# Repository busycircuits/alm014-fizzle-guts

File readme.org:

* ALM014 FIZZLE GUTS

[[alm014.png]]

** Introduction

The ALM Busy Circuits 'Fizzle guts' is a Eurorack dual low pass filter
and VCA that uses a 'donor' filter MB87186 chip from a Casio FZ1
sampler. It was originally designed in 2014 as a fun side project and
only approx 30 of the original units were made. With no plans to make
any more, we have open sourced the pcb design files (eagle), avr
microcontroller code and a basic panel design so others can make there
own and add customisations and/or improvements.

A built module features two filter cores A & B with voltage and direct
controlled resonance and cut off as well as a 'DCA' (a digital
controlled vca). There is also a mix output. Expect a weird murky
sounding filter which can squeek and blip when modulated but can
really squelch up nice.

You will need a donor 'MB87186' IC desolded from a real FZ1 or FZ1M
synth. They each contain 4 and the IC is usually marked 'FM1' with a
date code below. The IC then connects to the DIL socket on the rear of
the module.

For more information on the MB87186 (and from what much of the code
was based on) see http://www.buchty.net/casio/dcf.html

*PLEASE NOTE EVERYTHING IS PROVIDED AS IS. WE ARE UNABLE PROVIDE ANY SUPPORT TO ANYONE ATTEMPTING TO USE THESE FILES*

** Building and flashing the firmware

You'll need a basic 'usbtiny' AVR programmer.

You'll need to install avr-gcc and avrdude.

/(On mac using brew..)/
#+BEGIN_SRC
brew tap osx-cross/avr
brew install avr-gcc
brew install avrdude
#+END_SRC

Type 'make' in the firmare/ directory to compile the source code and
then run './flash.sh' (with your programmer connected) to program the
Fizzle.

** License

Code: MIT license.

Hardware: cc-by-sa-3.0

** Guidelines for derivative works

*ALM is a registered trademark.*

The name "ALM" should not be used on any of the derivative works you create from these files.

We kindly ask to do not name any derivatives 'FIZZLE GUTS' but give it a new name.

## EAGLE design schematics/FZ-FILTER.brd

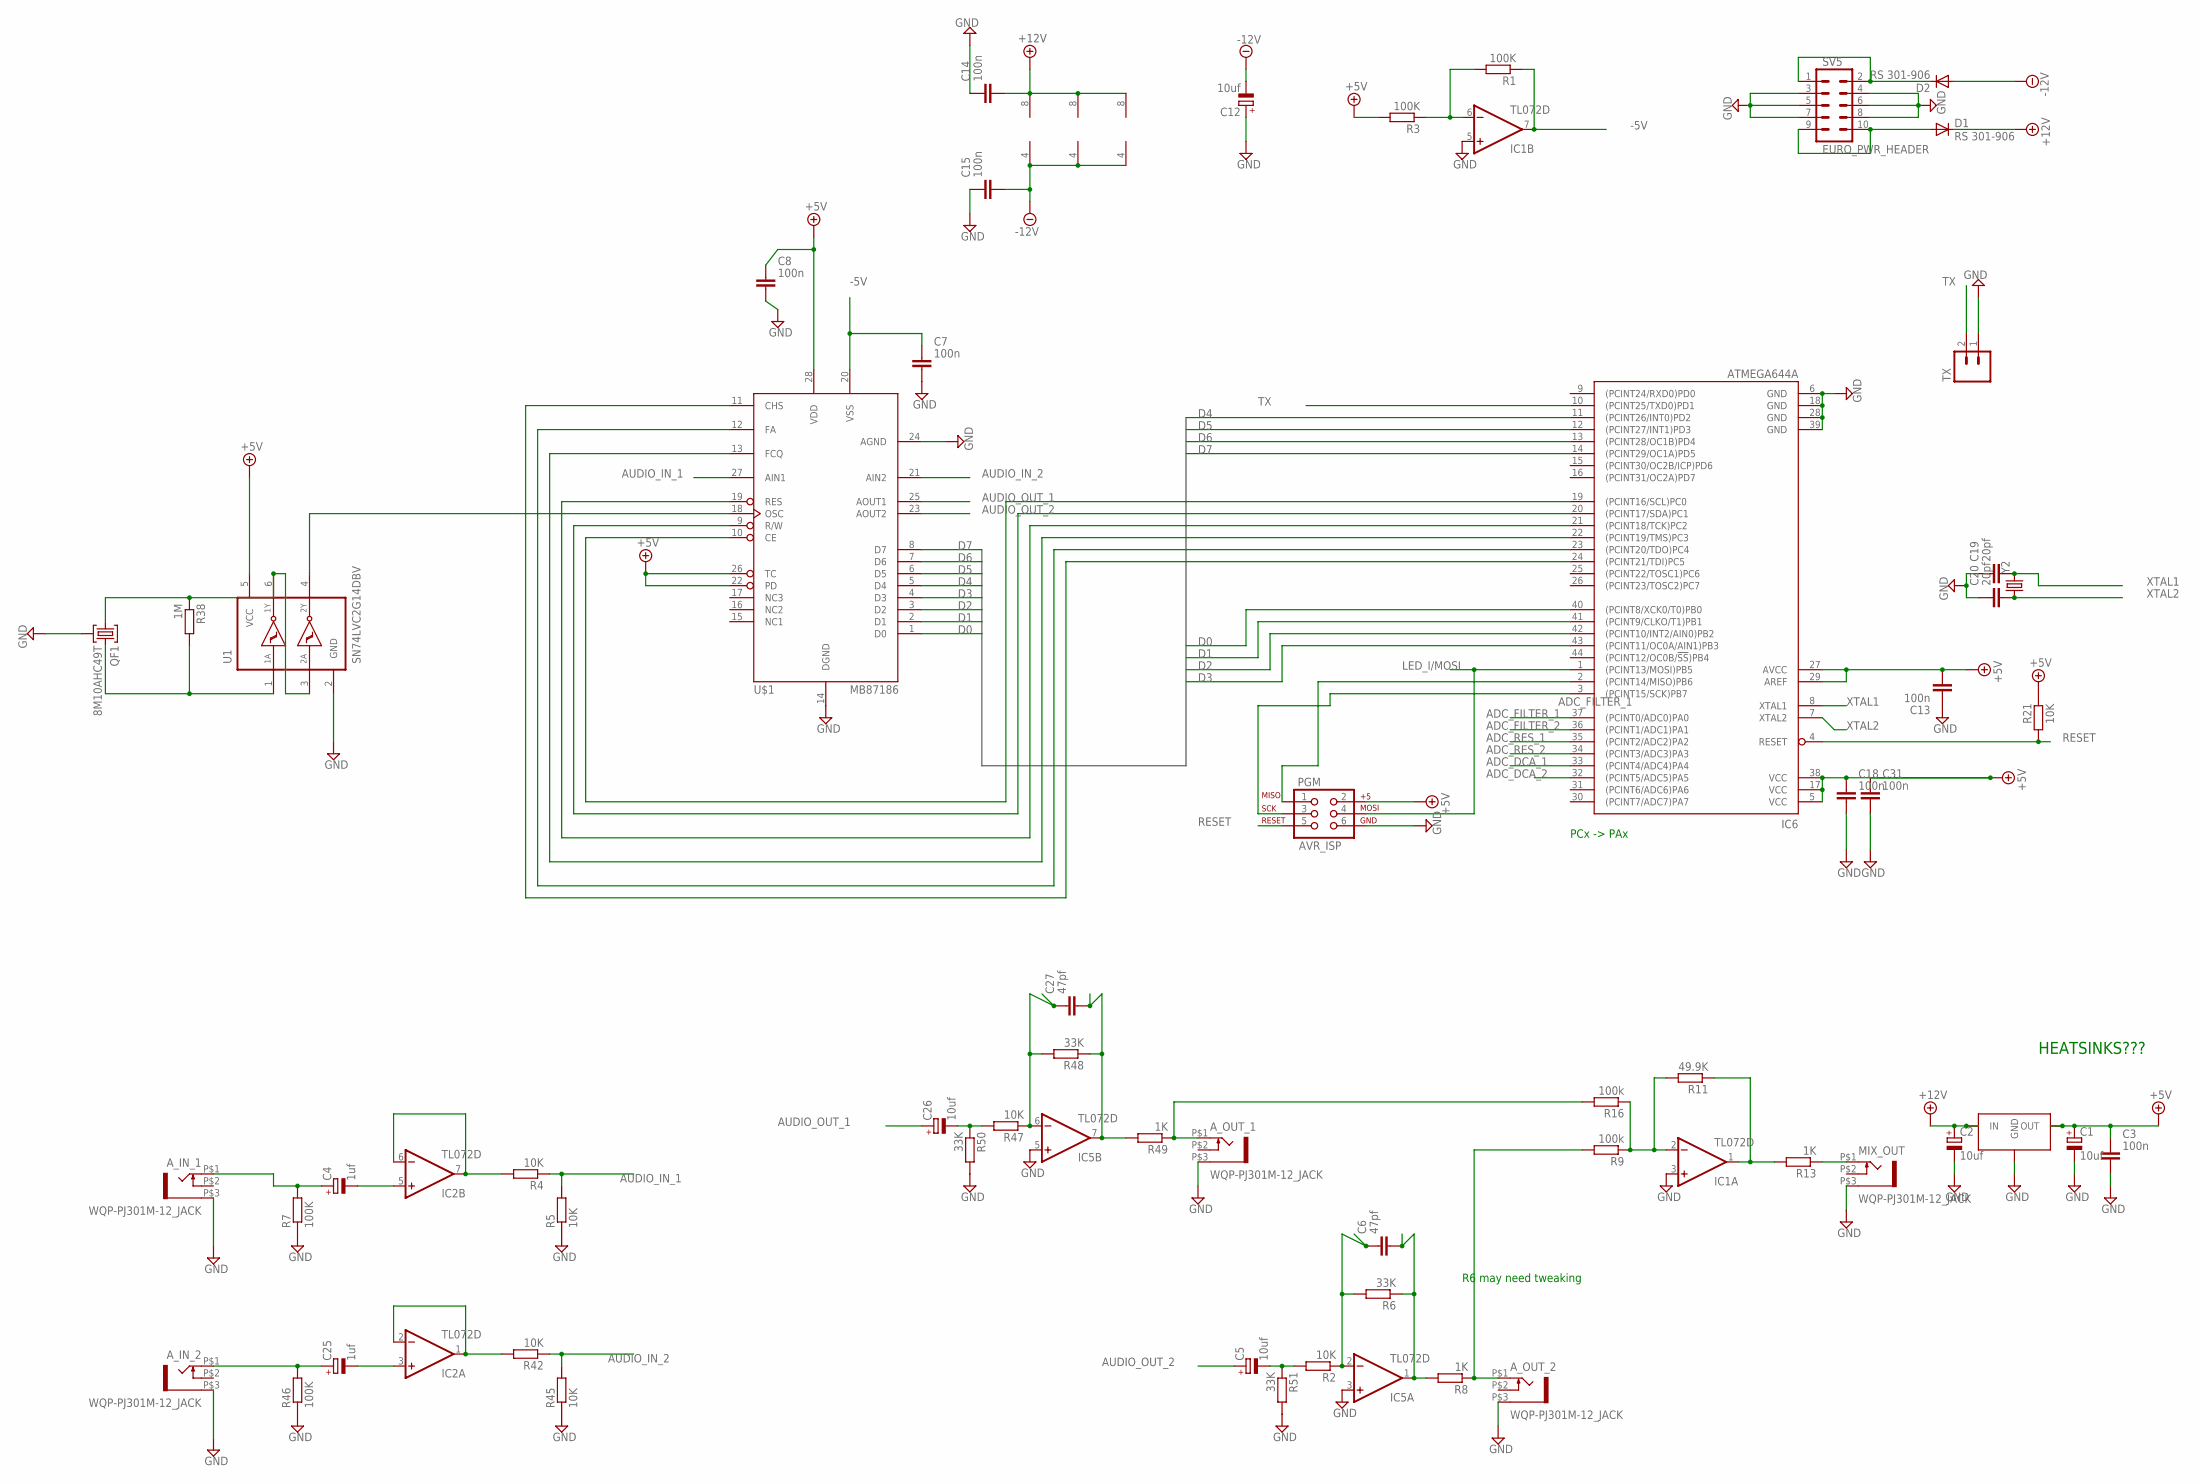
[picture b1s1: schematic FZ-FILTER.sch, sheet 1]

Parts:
A_IN_1, A_IN_2: WQP-PJ301M-12_JACK
A_OUT_1, A_OUT_2: WQP-PJ301M-12_JACK
C1, C2, C5, C12, C26: 10uf; PANASONIC_B
C3, C7, C8, C13, C14, C15, C18, C31: 100n; C0603
C4, C25: 1uf; PANASONIC_B
C6, C27: 47pf; C0603
C19, C20: 20pf; C0603
D1, D2: RS 301-906; SMB-DIODE
IC1, IC2, IC5: TL072D; SO08
IC6: ATMEGA644A; TQFP44
MIX_OUT: WQP-PJ301M-12_JACK
PGM: AVR_ISP; 2X3
QF1: 8M10AHC49T; HC49U
R1, R3, R7, R46: 100K; R0603
R2, R4, R5, R21, R42, R45, R47: 10K; R0603
R6, R48, R50, R51: 33K; R0603
R8, R13, R49: 1K; R0603
R9, R16: 100k; R0603
R11: 49.9K; R0603
R38: 1M; R0603
SV5: EURO_PWR_HEADER
TX: M02PTH; 1X02
U1: SN74LVC2G14DBV; SOT23-6
U3: 7805; VREG-7805-DPAK2
U$1: MB87186; DIP28
Y2: CRYSTALSMD; HC49UP

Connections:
+5V: C1.+, C3.1, C8.1, C13.2, C18.1, C31.1, IC6.5 (VCC), IC6.17 (VCC), IC6.27 (AVCC), IC6.29 (AREF), IC6.38 (VCC), PGM.2, R3.2, R21.2, U1.5 (VCC), U3.VOUT (OUT), U$1.22 (PD), U$1.26 (TC), U$1.28 (VDD); also elsewhere on the board
+12V: C2.+, C14.2, D1.C, IC1.8 (V+), IC2.8 (V+), IC5.8 (V+), U3.VIN (IN); also elsewhere on the board
-5V: C7.1, IC1.7 (OUT), R1.1, U$1.20 (VSS); also elsewhere on the board
-12V: C12.-, C15.2, D2.A, IC1.4 (V-), IC2.4 (V-), IC5.4 (V-); also elsewhere on the board
ADC_DCA_1: IC6.33 ((PCINT4/ADC4)PA4); also elsewhere on the board
ADC_DCA_2: IC6.32 ((PCINT5/ADC5)PA5); also elsewhere on the board
ADC_FILTER_1: IC6.37 ((PCINT0/ADC0)PA0); also elsewhere on the board
ADC_FILTER_2: IC6.36 ((PCINT1/ADC1)PA1); also elsewhere on the board
ADC_MISO: IC6.2 ((PCINT14/MISO)PB6), PGM.1
ADC_RES_1: IC6.35 ((PCINT2/ADC2)PA2); also elsewhere on the board
ADC_RES_2: IC6.34 ((PCINT3/ADC3)PA3); also elsewhere on the board
ADC_SCK: IC6.3 ((PCINT15/SCK)PB7), PGM.3
AUDIO_IN_1: R4.1, R5.2, U$1.27 (AIN1)
AUDIO_IN_2: R42.1, R45.2, U$1.21 (AIN2)
AUDIO_OUT_1: C26.+, U$1.25 (AOUT1)
AUDIO_OUT_2: C5.+, U$1.23 (AOUT2)
D0: IC6.40 ((PCINT8/XCK0/T0)PB0), U$1.1 (D0)
D1: IC6.41 ((PCINT9/CLKO/T1)PB1), U$1.2 (D1)
D2: IC6.42 ((PCINT10/INT2/AIN0)PB2), U$1.3 (D2)
D3: IC6.43 ((PCINT11/OC0A/AIN1)PB3), U$1.4 (D3)
D4: IC6.11 ((PCINT26/INT0)PD2), U$1.5 (D4)
D5: IC6.12 ((PCINT27/INT1)PD3), U$1.6 (D5)
D6: IC6.13 ((PCINT28/OC1B)PD4), U$1.7 (D6)
D7: IC6.14 ((PCINT29/OC1A)PD5), U$1.8 (D7)
GND: A_IN_1.P$3 (1), A_IN_2.P$3 (1), A_OUT_1.P$3 (1), A_OUT_2.P$3 (1), C1.-, C2.-, C3.2, C7.2, C8.2, C12.+, C13.1, C14.1, C15.1, C18.2, C19.1, C20.1, C31.2, IC1.3 (+IN), IC1.5 (+IN), IC5.3 (+IN), IC5.5 (+IN), IC6.6 (GND), IC6.18 (GND), IC6.28 (GND), IC6.39 (GND), MIX_OUT.P$3 (1), PGM.6, QF1.2, R5.1, R7.1, R45.1, R46.1, R50.2, R51.2, SV5.3, SV5.4, SV5.5, SV5.6, SV5.7, SV5.8, TX.1, U1.2 (GND), U3.GND, U$1.14 (DGND), U$1.24 (AGND); also elsewhere on the board
LED_I/MOSI: IC6.1 ((PCINT13/MOSI)PB5), PGM.4
unnamed: D2.C, SV5.1, SV5.2
unnamed: IC1.6 (-IN), R1.2, R3.1
unnamed: D1.A, SV5.9, SV5.10
unnamed: IC2.6 (-IN), IC2.7 (OUT), R4.2
unnamed: C6.1, IC5.2 (-IN), R2.1, R6.2
unnamed: C6.2, IC5.1 (OUT), R6.1, R8.2
unnamed: C5.-, R2.2, R51.1
unnamed: A_OUT_1.P$1 (2), R16.2, R49.1
unnamed: IC1.2 (-IN), R9.1, R11.2, R16.1
unnamed: IC1.1 (OUT), R11.1, R13.2
unnamed: A_OUT_2.P$1 (2), R8.1, R9.2
unnamed: C4.-, IC2.5 (+IN)
unnamed: A_IN_1.P$1 (2), C4.+, R7.2
unnamed: C25.-, IC2.3 (+IN)
unnamed: IC2.1 (OUT), IC2.2 (-IN), R42.2
unnamed: A_IN_2.P$1 (2), C25.+, R46.2
unnamed: C27.1, IC5.6 (-IN), R47.1, R48.2
unnamed: C27.2, IC5.7 (OUT), R48.1, R49.2
unnamed: C26.-, R47.2, R50.1
unnamed: MIX_OUT.P$1 (2), R13.1
unnamed: IC6.19 ((PCINT16/SCL)PC0), U$1.10 (CE)
unnamed: IC6.20 ((PCINT17/SDA)PC1), U$1.9 (R/W)
unnamed: IC6.21 ((PCINT18/TCK)PC2), U$1.19 (RES)
unnamed: IC6.22 ((PCINT19/TMS)PC3), U$1.13 (FCQ)
unnamed: IC6.23 ((PCINT20/TDO)PC4), U$1.12 (FA)
unnamed: IC6.24 ((PCINT21/TDI)PC5), U$1.11 (CHS)
unnamed: U1.4 (2Y), U$1.18 (OSC)
unnamed: QF1.1, R38.1, U1.3 (2A), U1.6 (1Y)
unnamed: QF1.3, R38.2, U1.1 (1A)
RESET: IC6.4 (RESET), PGM.5, R21.1
TX: IC6.10 ((PCINT25/TXD0)PD1), TX.2
XTAL1: C19.2, IC6.8 (XTAL1), Y2.2
XTAL2: C20.2, IC6.7 (XTAL2), Y2.1

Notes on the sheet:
PCx -> PAx
HEATSINKS???
R6 may need tweaking

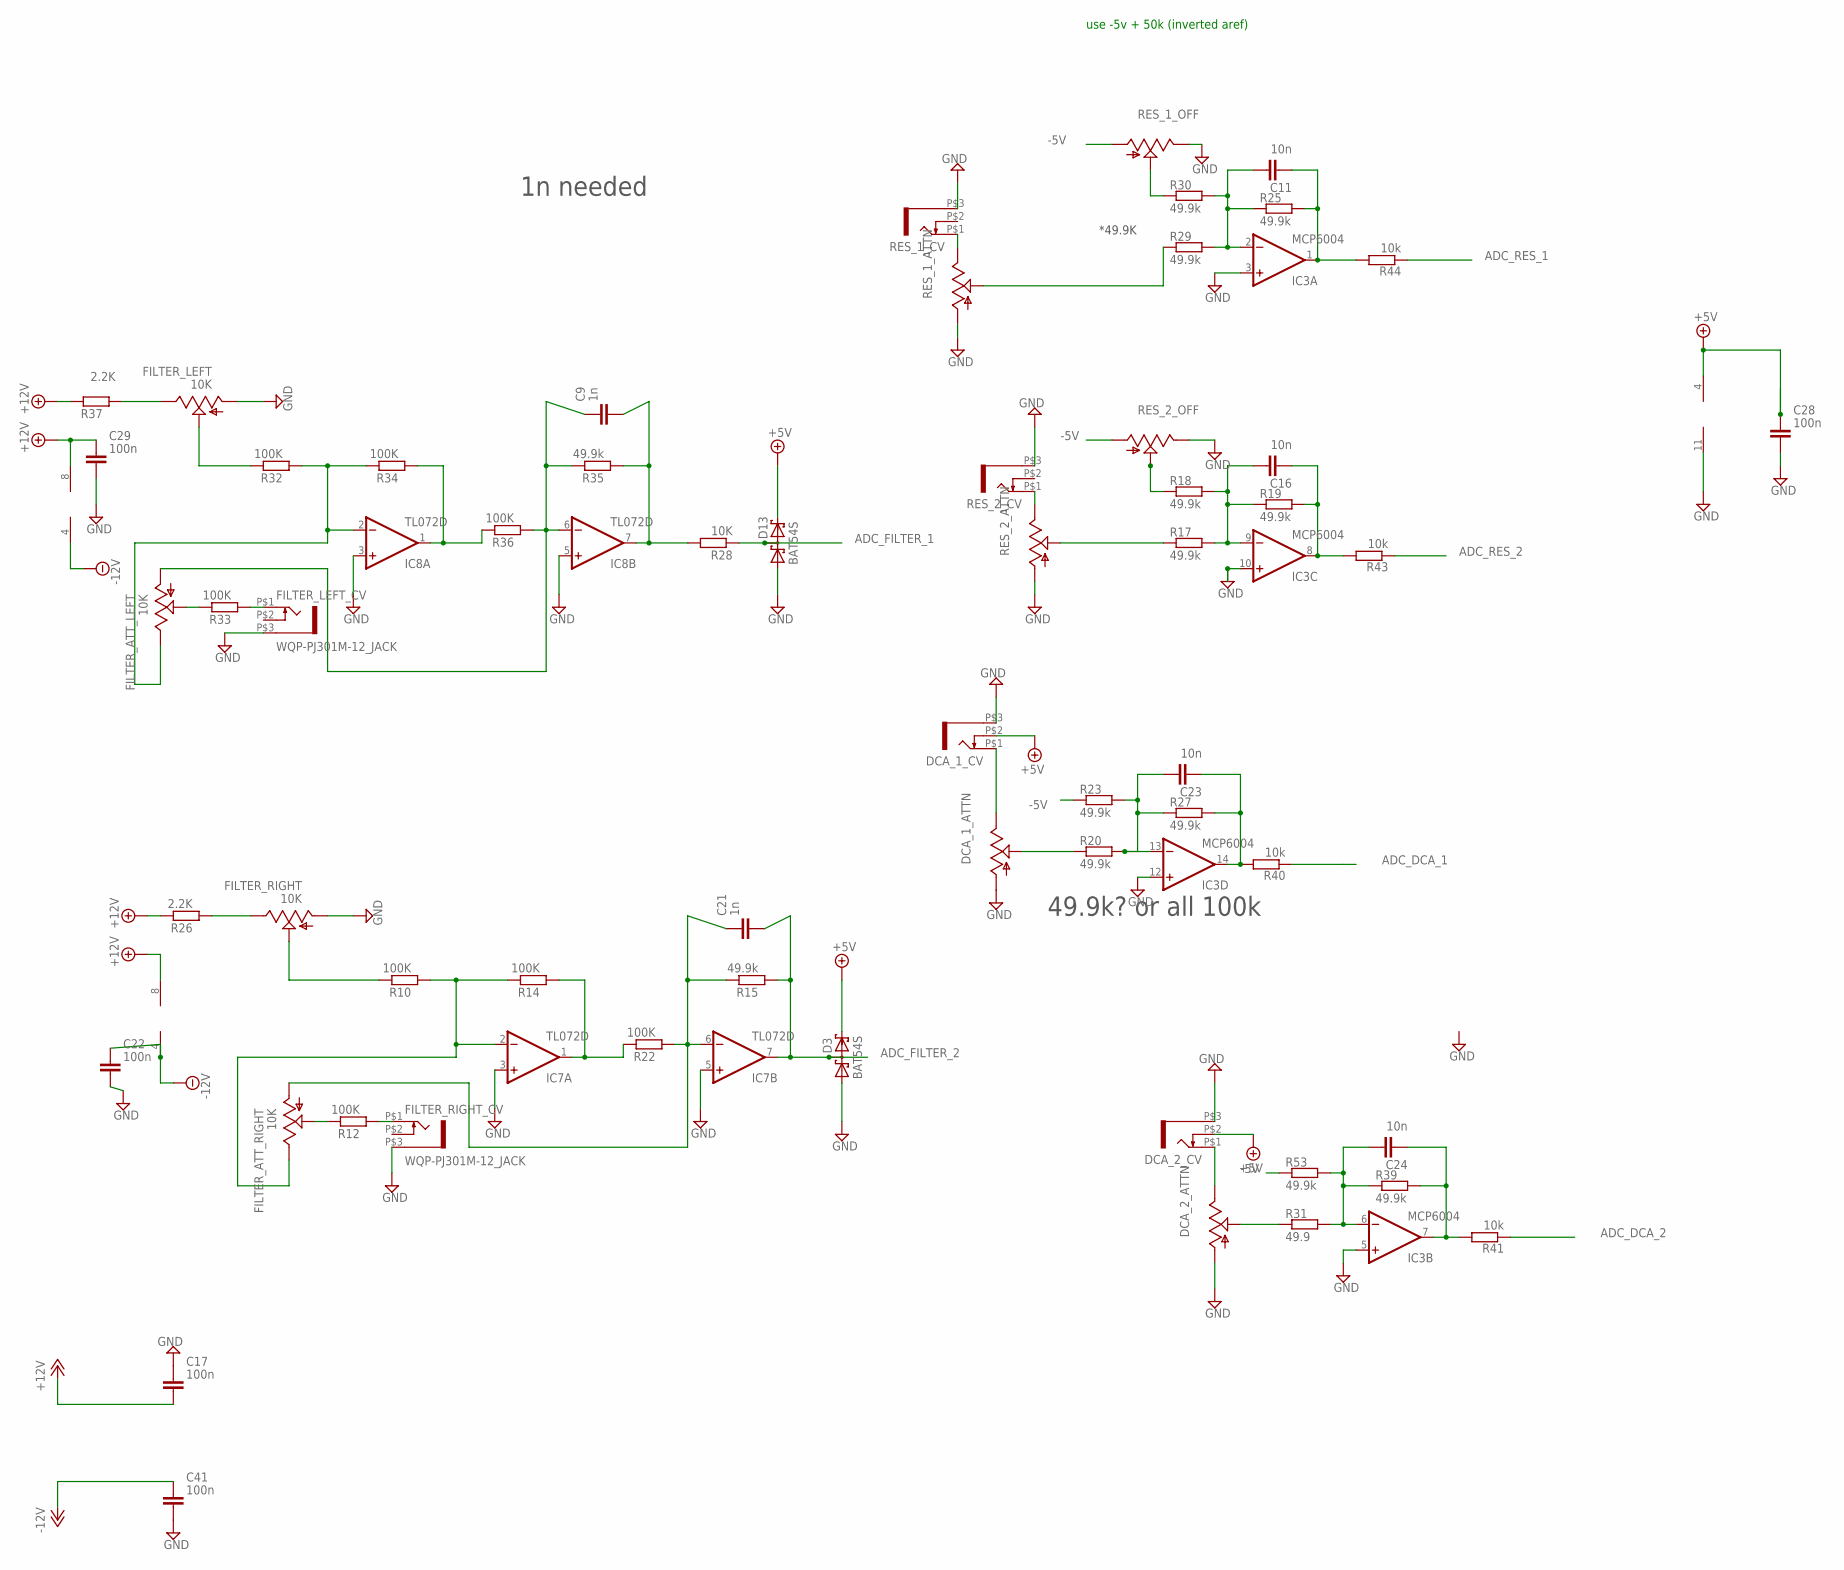
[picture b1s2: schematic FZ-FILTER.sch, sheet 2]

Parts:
C9, C21: 1n; C0603
C11, C16, C23, C24: 10n; C0603
C17, C22, C28, C29, C41: 100n; C0603
D3, D13: BAT54S; SOT23
DCA_1_ATTN, DCA_2_ATTN: ALPHA-9MMA; EVUF
DCA_1_CV, DCA_2_CV: WQP-PJ301M-12_JACK
FILTER_ATT_LEFT: 10K; EVUF
FILTER_ATT_RIGHT: 10K; EVUF
FILTER_LEFT: 10K; EVUF
FILTER_LEFT_CV: WQP-PJ301M-12_JACK
FILTER_RIGHT: 10K; EVUF
FILTER_RIGHT_CV: WQP-PJ301M-12_JACK
IC3: MCP6004; SO14
IC7, IC8: TL072D; SO08
R10, R12, R14, R22, R32, R33, R34, R36: 100K; R0603
R15, R17, R18, R19, R20, R23, R25, R27, R29, R30, R35, R39, R53: 49.9k; R0603
R26, R37: 2.2K; R0603
R28: 10K; R0603
R31: 49.9; R0603
R40, R41, R43, R44: 10k; R0603
RES_1_ATTN, RES_1_OFF, RES_2_ATTN, RES_2_OFF: ALPHA-9MMA; EVUF
RES_1_CV, RES_2_CV: WQP-PJ301M-12_JACK

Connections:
+5V: C28.1, D3.2 (C2), D13.2 (C2), DCA_1_CV.P$2 (3), DCA_2_CV.P$2 (3), IC3.4 (V+); also elsewhere on the board
+12V: C17.2, C29.1, IC7.8 (V+), IC8.8 (V+), R26.2, R37.2; also elsewhere on the board
-5V: R23.1, R53.1, RES_1_OFF.1 (A), RES_2_OFF.1 (A); also elsewhere on the board
-12V: C22.1, C41.1, IC7.4 (V-), IC8.4 (V-); also elsewhere on the board
ADC_DCA_1: R40.1; also elsewhere on the board
ADC_DCA_2: R41.1; also elsewhere on the board
ADC_FILTER_1: D13.3 (C1A2), R28.1; also elsewhere on the board
ADC_FILTER_2: C21.2, D3.3 (C1A2), IC7.7 (OUT), R15.1; also elsewhere on the board
ADC_RES_1: R44.1; also elsewhere on the board
ADC_RES_2: R43.1; also elsewhere on the board
GND: C17.1, C22.2, C28.2, C29.2, C41.2, D3.1 (A1), D13.1 (A1), DCA_1_ATTN.1 (A), DCA_1_CV.P$3 (1), DCA_2_ATTN.1 (A), DCA_2_CV.P$3 (1), FILTER_LEFT.1 (A), FILTER_LEFT_CV.P$3 (1), FILTER_RIGHT.1 (A), FILTER_RIGHT_CV.P$3 (1), IC3.3 (+IN), IC3.5 (+IN), IC3.10 (+IN), IC3.11 (V-), IC3.12 (+IN), IC7.3 (+IN), IC7.5 (+IN), IC8.3 (+IN), IC8.5 (+IN), RES_1_ATTN.1 (A), RES_1_CV.P$3 (1), RES_1_OFF.3 (E), RES_2_ATTN.1 (A), RES_2_CV.P$3 (1), RES_2_OFF.3 (E); also elsewhere on the board
I7: C9.2, IC8.7 (OUT), R28.2, R35.1
unnamed: RES_1_ATTN.3 (E), RES_1_CV.P$1 (2)
unnamed: R30.1, RES_1_OFF.2 (S)
unnamed: C24.1, IC3.6 (-IN), R31.2, R39.1, R53.2
unnamed: C11.2, IC3.1 (OUT), R25.2, R44.2
unnamed: R29.1, RES_1_ATTN.2 (S)
unnamed: DCA_1_ATTN.3 (E), DCA_1_CV.P$1 (2)
unnamed: C16.1, IC3.9 (-IN), R17.2, R18.2, R19.1
unnamed: R18.1, RES_2_OFF.2 (S)
unnamed: RES_2_ATTN.3 (E), RES_2_CV.P$1 (2)
unnamed: C23.1, IC3.13 (-IN), R20.2, R23.2, R27.1
unnamed: DCA_1_ATTN.2 (S), R20.1
unnamed: DCA_2_ATTN.2 (S), R31.1
unnamed: C16.2, IC3.8 (OUT), R19.2, R43.2
unnamed: DCA_2_ATTN.3 (E), DCA_2_CV.P$1 (2)
unnamed: FILTER_RIGHT.2 (S), R10.2
unnamed: FILTER_ATT_RIGHT.3 (E), IC7.2 (-IN), R10.1, R14.2
unnamed: C11.1, IC3.2 (-IN), R25.1, R29.2, R30.2
unnamed: FILTER_RIGHT_CV.P$1 (2), R12.1
unnamed: FILTER_ATT_RIGHT.2 (S), R12.2
unnamed: IC7.1 (OUT), R14.1, R22.2
unnamed: C21.1, FILTER_ATT_RIGHT.1 (A), IC7.6 (-IN), R15.2, R22.1
unnamed: FILTER_RIGHT.3 (E), R26.1
unnamed: FILTER_LEFT.2 (S), R32.2
unnamed: FILTER_ATT_LEFT.3 (E), IC8.2 (-IN), R32.1, R34.2
unnamed: FILTER_LEFT_CV.P$1 (2), R33.1
unnamed: IC8.1 (OUT), R34.1, R36.2
unnamed: C9.1, FILTER_ATT_LEFT.1 (A), IC8.6 (-IN), R35.2, R36.1
unnamed: FILTER_LEFT.3 (E), R37.1
unnamed: FILTER_ATT_LEFT.2 (S), R33.2
unnamed: R17.1, RES_2_ATTN.2 (S)
REL1_ADC: C23.2, IC3.14 (OUT), R27.2, R40.2
REL2_ADC: C24.2, IC3.7 (OUT), R39.2, R41.2

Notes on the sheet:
use -5v + 50k (inverted aref)
49.9k? or all 100k
1n needed
*49.9K

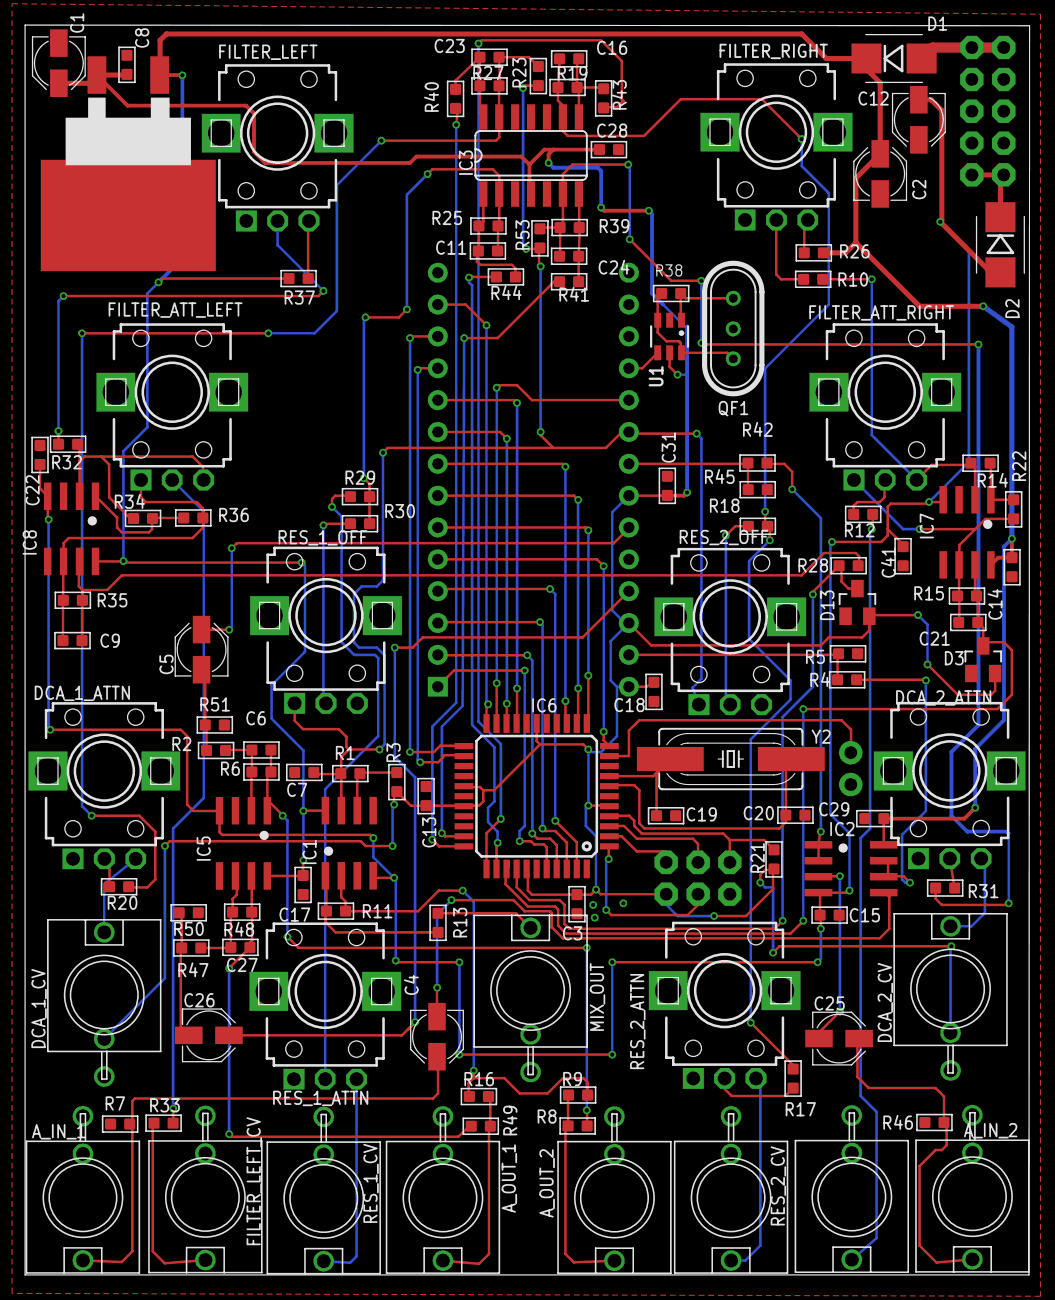
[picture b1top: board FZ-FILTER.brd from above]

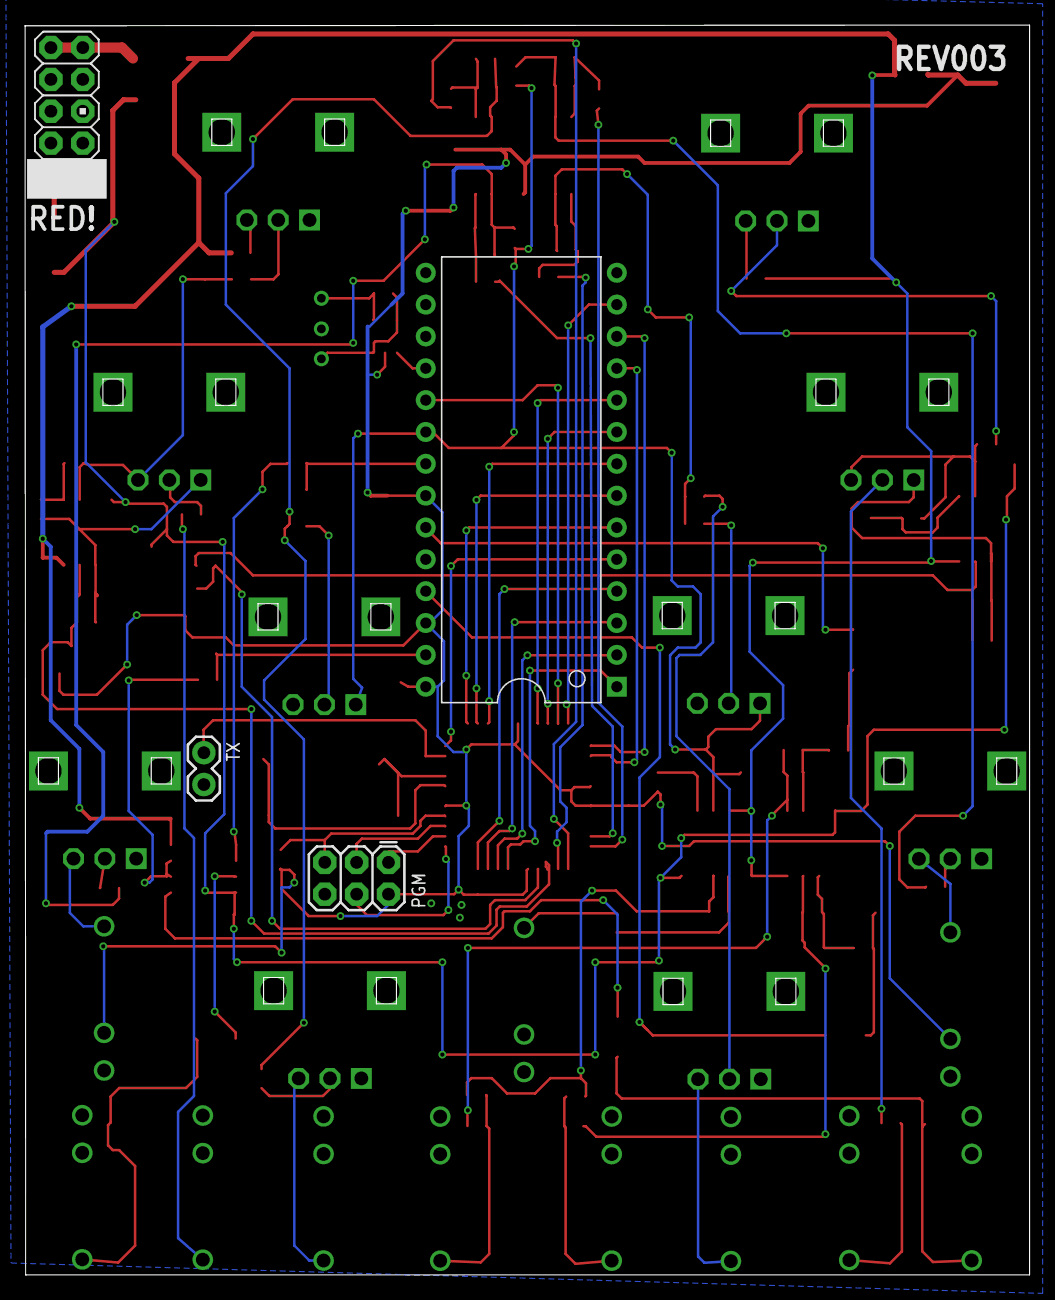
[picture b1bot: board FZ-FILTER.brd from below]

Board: 2 copper layers, 80.1 x 99.7 mm, 122 parts (5 on the bottom side), 92 nets.

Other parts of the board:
U$2: LOGO_WEEE

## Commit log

2022-10-12 Initial import
2022-10-12 remove temp file
2022-10-12 Add image and work on readme
2022-10-13 readme updates
2022-10-29 minor readme updates and rename form directory
2023-03-09 Update BOM with missing QF1 resonator
2024-02-07 gerbers for ordering PCB

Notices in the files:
parts and their libraries:
SparkFun: Licensing: CC v3.0 Share-Alike You are welcome to use this library for commercial purposes.
74LV: Copyright (C) 2008, Bob Starr
